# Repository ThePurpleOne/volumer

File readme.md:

# Volumer
Hardware module to easily control Individual Windows app just like the volume Mixer.

Accessing this window is a pain, especially if you're in game and you need to quickly lower that annoying SCREAMING discord friend in order to hear some terrorist footsteps.

> The PCB parts have been chosen for cheapest PCB Assembly with only 2 JLC PCB extended parts 

## How to setup
First you have to order your PCB and mount the potentiometers:
- [PCB Information](pcbs.md)
- [JLC PCB Order instructions](jlc_order.md)

Then you can install the software on the PC and flash the firmware on the Board:
- [Install the PC app](#pc-software)
- [Install/Update Board Firmware](#board-firmware)

## Case

There is no case for now, don't hesitate to contribute ! Here is the dimensions

## PC Software

[https://github.com/omriharel/deej](https://github.com/omriharel/deej)

For simplicity and not to reinvent the wheel, I'm using an opensource project called DEEJ, which actually does exactly what I want to do.

You only need to put the executable in the same folder as the config file and make a shortcut to the executable in the startup folder to have it start with windows.

config : [./src/pc/config.yaml](./src/pc/config.yaml) 

In the config, You can set which potentiometer controls which application and set the COM port of the board (The COM port is not automatically detected).

## Board Firmware 
You Circuit python or a UF2 compiled C program are available in the release page.

### C firmware
There is an already compiled UF2 file in the releases.

You can also compile the code yourself (need the RPI PICO SDK) and flash it to the board (Drag'n'drop in BOOTSEL mode). 

Compile with:
```bash
cd src/board/c
mkdir build
cd build
cmake ..
make
```

You can then flash the board with the generated UF2 file in the bin folder.

### Circuit Python
You can also use Circuitpython, which for a firmware that simple, i would not recommend it since it's just less reliable and efficient.

You'll first need to install Circuitpython firmware in the board and then push the program into it (Firmware and program available in release). 

To install the circuitpython firmware, you can simply drag and drop the UF2 file on the board after a boot with the BOOTSEL button pressed.

When Circuitpython is running, you can drag and drop the code.py file into the board Circuitpython mass storage (Not the one when bootsel is pressed).

## Download repo
Since there are submodules, you need to clone with the --recurse-submodules flag:

```bash
git clone --recurse-submodules
```

If you cloned without submodules
```bash
git submodule update --init
```

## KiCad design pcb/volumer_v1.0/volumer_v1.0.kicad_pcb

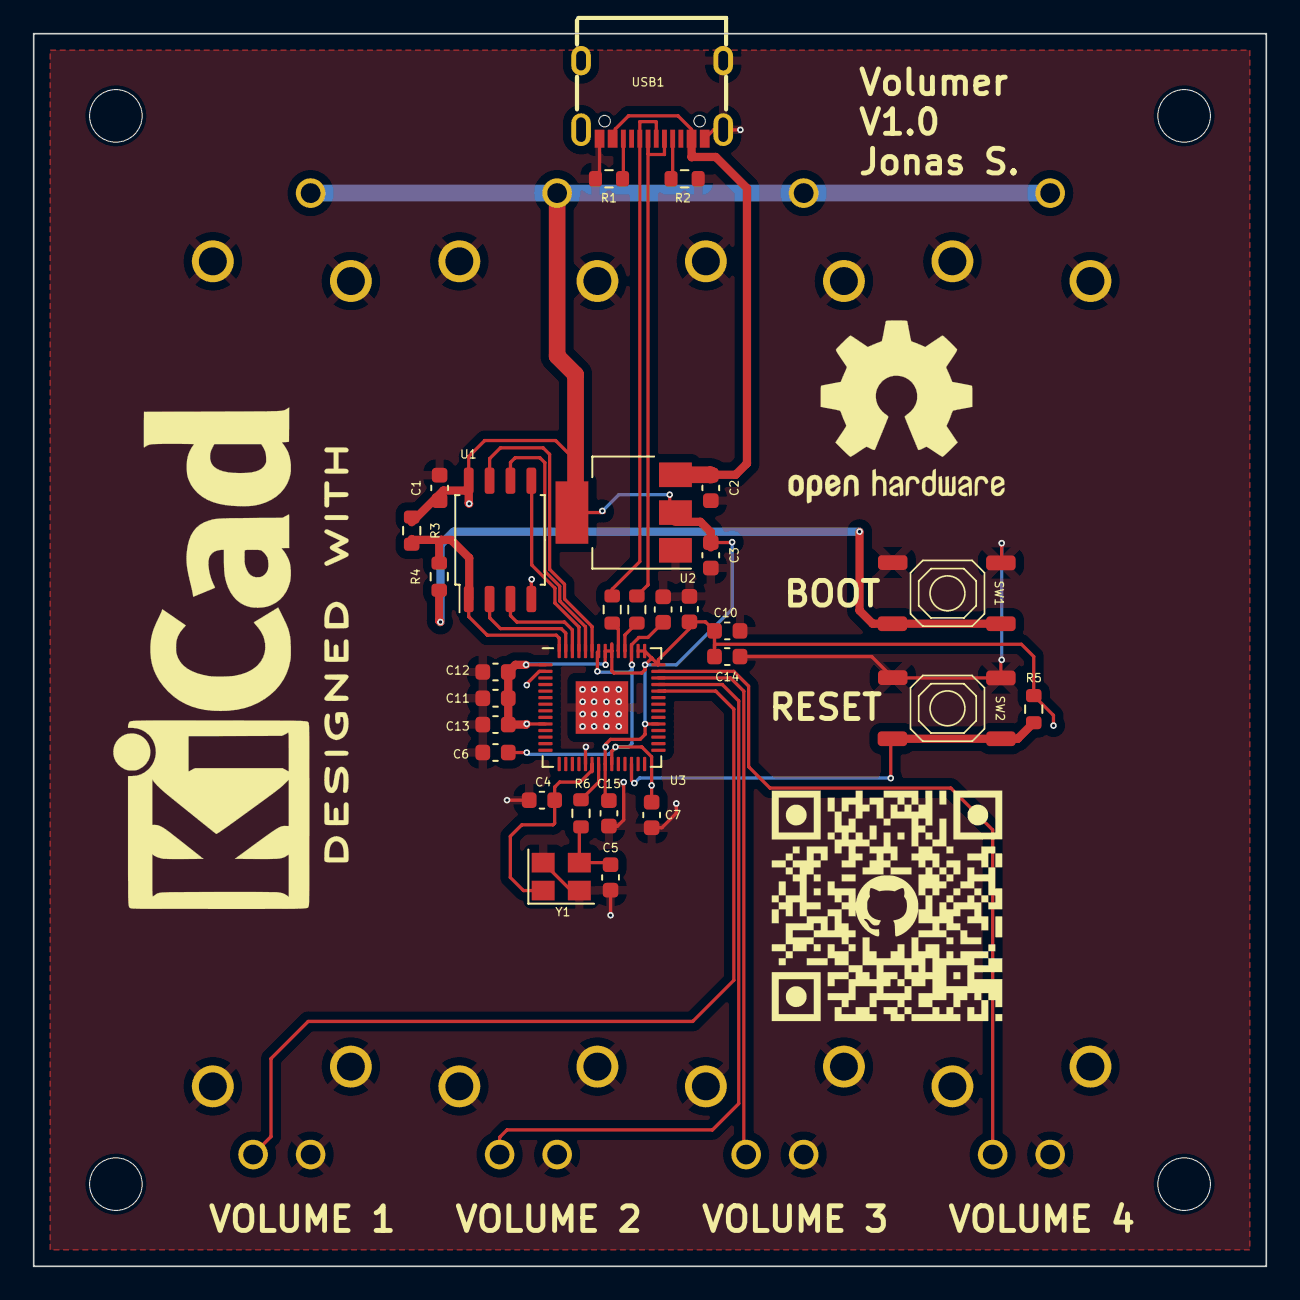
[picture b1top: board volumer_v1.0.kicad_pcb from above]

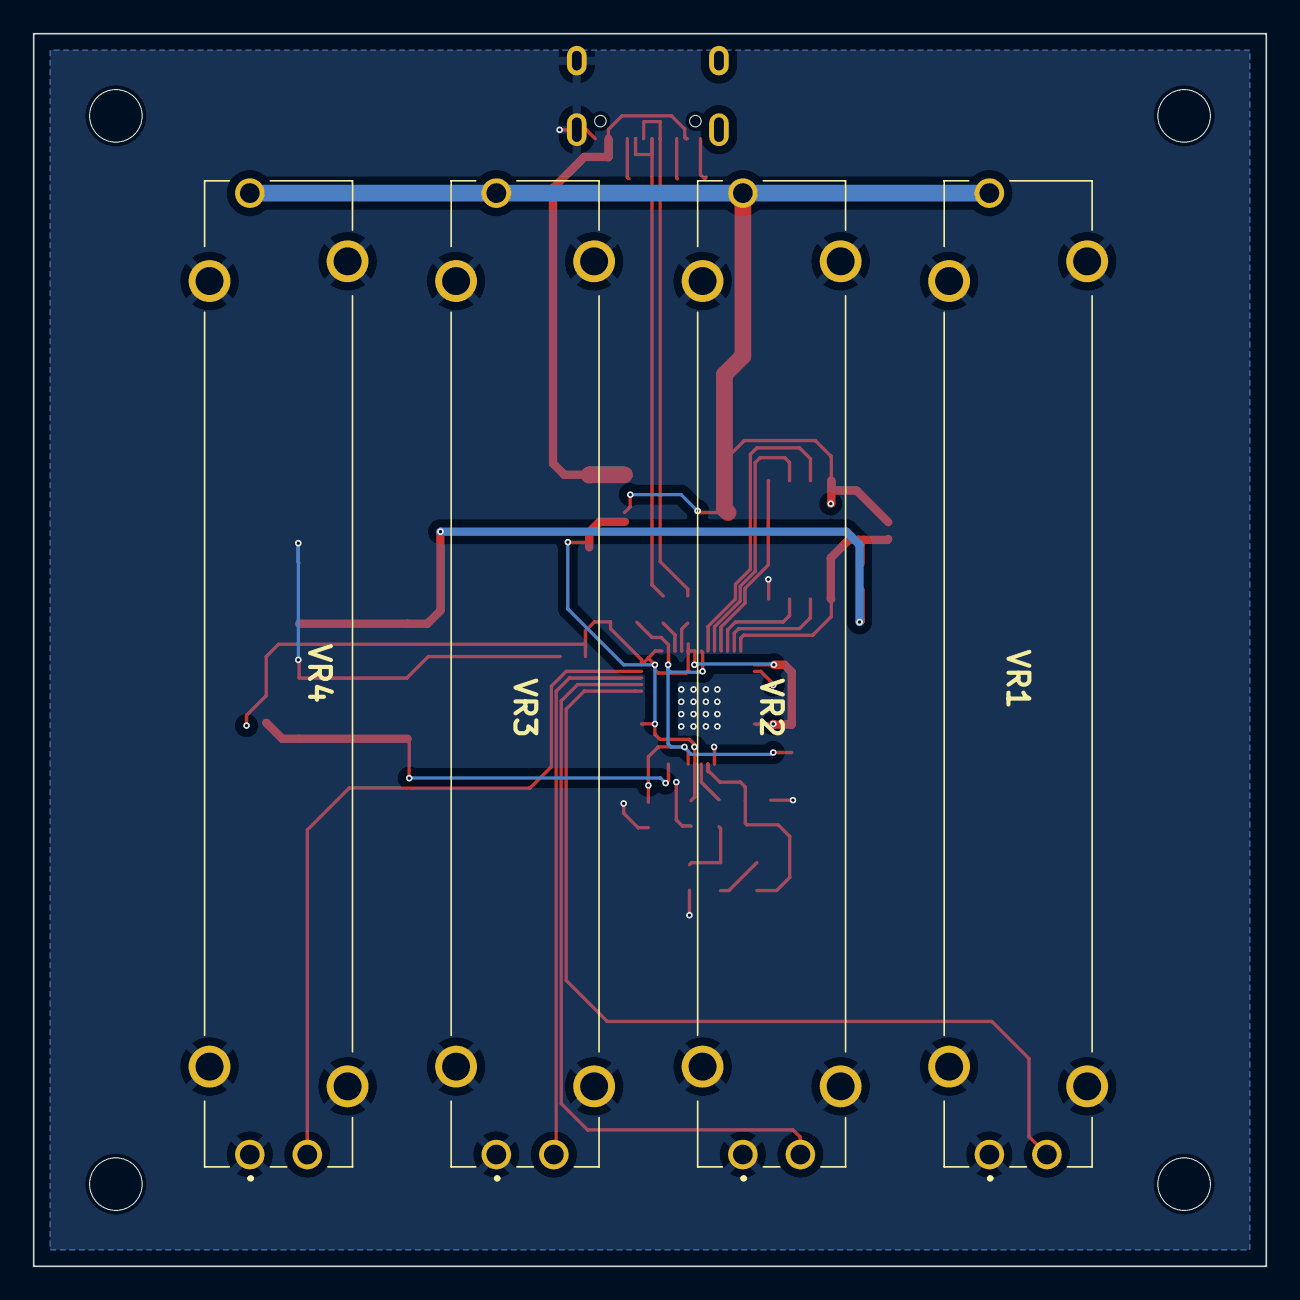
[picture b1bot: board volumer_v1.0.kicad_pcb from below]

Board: 2 copper layers, 75.0 x 75.0 mm, 39 parts (4 on the bottom side), 25 nets.

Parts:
C1, C2, C6, C7, C10, C11, C12, C13, C14, C15: 100n; C_0603_1608Metric
C3: 10u; C_0603_1608Metric
C4, C5: 30p; C_0603_1608Metric
C8, C9: 1u; C_0603_1608Metric
MH: MountingHole_3.2mm_M3
MH#2, MH#3, MH#4: MountingHole_3.2mm_M3
QR: LOGO; qr
R1, R2: 5k1; R_0603_1608Metric
R3, R5: 10k; R_0603_1608Metric
R4, R6: 1k; R_0603_1608Metric
R7, R8: 33; R_0603_1608Metric
SW1, SW2: SW_MEC_5E; TS-1187A-B-A-B
U1: W25Q128JVS; SOIC-8_5.23x5.23mm_P1.27mm
U2: LD1117S33TR; SOT-223-3_TabPin2
U3: RP2040; QFN-56-1EP_7x7mm_P0.4mm_EP3.2x3.2mm
USB1: USBC_16P
VR1, VR2, VR3, VR4: slide_pot; PTA45432015CPB503
Y1: 12Mhz; Crystal_SMD_3225-4Pin_3.2x2.5mm

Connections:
+3V3: C1.1, C3.1, C9.1, C10.1, C11.1, C12.1, C13.1, C14.1, C15.1, R3.1, R5.1, U1.8 (VCC), U2.2 (VO), U3.1 (IOVDD), U3.10 (IOVDD), U3.22 (IOVDD), U3.33 (IOVDD), U3.42 (IOVDD), U3.43 (ADC_AVDD), U3.44 (VREG_IN), U3.48 (USB_VDD), U3.49 (IOVDD), VR1.3 (VCC), VR2.3 (VCC), VR3.3 (VCC), VR4.3 (VCC)
+5V: C2.1, U2.3 (VI), USB1.2 (VBUS), USB1.11 (VBUS)
/USB_D+: R7.2, USB1.6 (D+), USB1.8 (D+)
/USB_D-: R8.2, USB1.5 (D-), USB1.7 (D-)
/rp2040/1V1: C6.1, C7.1, C8.1, U3.23 (DVDD), U3.45 (VREG_VOUT), U3.50 (DVDD)
/rp2040/N_USB_D+: R7.1, U3.47 (USB_DP)
/rp2040/N_USB_D-: R8.1, U3.46 (USB_DM)
/rp2040/QSPI_CLK: U1.6 (CLK), U3.52 (QSPI_SCLK)
/rp2040/QSPI_SD0: U1.5 (DI(IO0)), U3.53 (QSPI_SD0)
/rp2040/QSPI_SD1: U1.2 (DO(IO1)), U3.55 (QSPI_SD1)
/rp2040/QSPI_SD2: U1.3 (IO2), U3.54 (QSPI_SD2)
/rp2040/QSPI_SD3: U1.7 (IO3), U3.51 (QSPI_SD3)
/rp2040/QSPI_SS: R3.2, R4.2, U1.1 (~CS), U3.56 (QSPI_SS)
/rp2040/XIN: C4.1, U3.20 (XIN), Y1.1
/rp2040/XOUT: R6.1, U3.21 (XOUT)
/rp2040/~RST: R5.2, SW2.3 (K), SW2.4 (A), U3.26 (RUN)
/rp2040/~USB_BOOT: R4.1, SW1.3 (K), SW1.4 (A)
/vol_1: U3.38 (GPIO26_ADC0), VR1.2 (WP)
/vol_2: U3.39 (GPIO27_ADC1), VR2.2 (WP)
/vol_3: U3.40 (GPIO28_ADC2), VR3.2 (WP)
/vol_4: U3.41 (GPIO29_ADC3), VR4.2 (WP)
GND: C1.2, C2.2, C3.2, C4.2, C5.2, C6.2, C7.2, C8.2, C9.2, C10.2, C11.2, C12.2, C13.2, C14.2, C15.2, R1.2, R2.2, SW1.1, SW1.2, SW2.1, SW2.2, U1.4 (GND), U2.1 (GND), U3.19 (TESTEN), U3.57 (GND), USB1.1 (GND), USB1.12 (GND), USB1.13 (SHLD), VR1.1 (GND), VR1.MH1, VR1.MH2, VR1.MH3, VR1.MH4, VR2.1 (GND), VR2.MH1, VR2.MH2, VR2.MH3, VR2.MH4, VR3.1 (GND), VR3.MH1, VR3.MH2, VR3.MH3, VR3.MH4, VR4.1 (GND), VR4.MH1, VR4.MH2, VR4.MH3, VR4.MH4, Y1.2, Y1.4
unnamed: C5.1, R6.2, Y1.3
unnamed: R2.1, USB1.4 (CC1)
unnamed: R1.1, USB1.10 (CC2)

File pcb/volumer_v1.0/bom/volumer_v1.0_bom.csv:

"Reference","Value","Footprint","Qty","LCSC"
"C1,C2,C6,C7,C10,C11,C12,C13,C14,C15","100n","Capacitor_SMD:C_0603_1608Metric","10","C14663"
"C3","10u","Capacitor_SMD:C_0603_1608Metric","1","C19702"
"C4,C5","30p","Capacitor_SMD:C_0603_1608Metric","2","C1658"
"C8,C9","1u","Capacitor_SMD:C_0603_1608Metric","2","C15849"
"R1,R2","5k1","Resistor_SMD:R_0603_1608Metric","2","C23186"
"R3,R5","10k","Resistor_SMD:R_0603_1608Metric","2","C25804"
"R4,R6","1k","Resistor_SMD:R_0603_1608Metric","2","C21190"
"R7,R8","33","Resistor_SMD:R_0603_1608Metric","2","C23140"
"SW1,SW2","SW_MEC_5E","push_button:TS-1187A-B-A-B","2","C318884"
"U1","W25Q128JVS","Package_SO:SOIC-8_5.23x5.23mm_P1.27mm","1","C97521"
"U2","LD1117S33TR","Package_TO_SOT_SMD:SOT-223-3_TabPin2","1","C6186"
"U3","RP2040","Package_DFN_QFN:QFN-56-1EP_7x7mm_P0.4mm_EP3.2x3.2mm","1","C2040"
"USB1","~","USBC:USBC_16P","1","C2765186"
"VR1,VR2,VR3,VR4","slide_pot","PTA45432015CPB503","4",""
"Y1","12Mhz","Crystal:Crystal_SMD_3225-4Pin_3.2x2.5mm","1","C9002"

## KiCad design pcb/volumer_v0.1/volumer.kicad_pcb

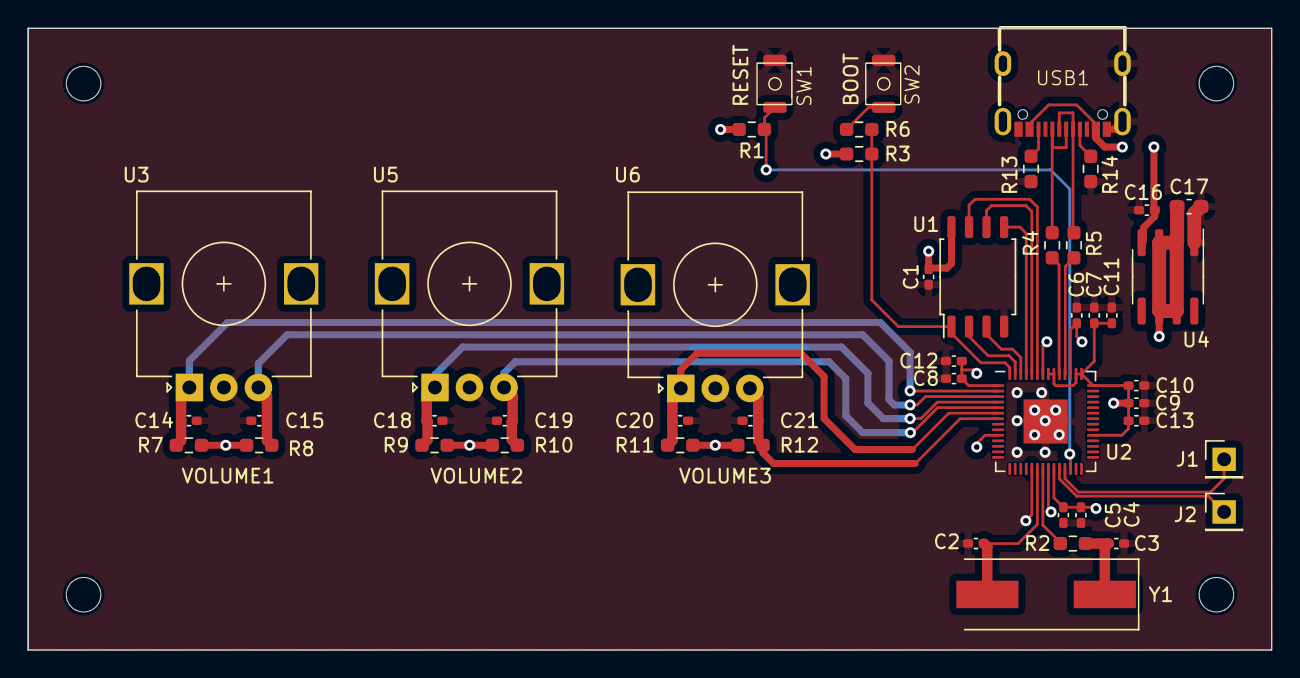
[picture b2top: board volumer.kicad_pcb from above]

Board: 4 copper layers, 90.0 x 45.0 mm, 47 parts (0 on the bottom side), 29 nets.

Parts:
C1, C4, C5, C8, C9, C10, C11, C12, C13, C16: 100n; C_0402_1005Metric_Pad0.74x0.62mm_HandSolder
C2, C3: 27p; C_0402_1005Metric_Pad0.74x0.62mm_HandSolder
C6, C7, C14, C15, C18, C19, C20, C21: 1u; C_0402_1005Metric_Pad0.74x0.62mm_HandSolder
C17: 10u; C_0603_1608Metric_Pad1.08x0.95mm_HandSolder
J1, J2: Conn_01x01_Pin; PinHeader_1x01_P2.54mm_Vertical
R1, R3, R7, R8, R9, R10, R11, R12: 10k; R_0603_1608Metric_Pad0.98x0.95mm_HandSolder
R2, R6: 1k; R_0603_1608Metric_Pad0.98x0.95mm_HandSolder
R4, R5: 27; R_0603_1608Metric_Pad0.98x0.95mm_HandSolder
R13, R14: 5k1; R_0603_1608Metric_Pad0.98x0.95mm_HandSolder
SW1, SW2: TS-3025-B-C-B; lcsc_TS-3025-A-A-B_push_button
U1: W25Q128JVS; SOIC-8_5.23x5.23mm_P1.27mm
U2: RP2040; QFN-56-1EP_7x7mm_P0.4mm_EP3.2x3.2mm
U3, U5, U6: Rotary encoder; RotaryEncoder_Alps_EC12E_Vertical_H20mm
U4: LD1117D33; SOIC-8_3.9x4.9mm_P1.27mm
USB1: USBC_16P
Y1: 12Mhz; Crystal_SMD_HC49-SD

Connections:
+3V3: C1.1, C7.1, C8.1, C9.1, C10.1, C11.1, C12.1, C13.1, C17.1, R1.1, R3.1, R7.1, R8.1, R9.1, R10.1, R11.1, R12.1, U1.8 (VCC), U2.1 (IOVDD), U2.10 (IOVDD), U2.22 (IOVDD), U2.33 (IOVDD), U2.42 (IOVDD), U2.43 (ADC_AVDD), U2.44 (VREG_IN), U2.48 (USB_VDD), U2.49 (IOVDD), U4.2 (VOUT), U4.3 (VOUT@2), U4.6 (VOUT@3), U4.7 (VOUT@4)
+5V: C16.1, U4.4 (VIN), USB1.2 (VBUS), USB1.11 (VBUS)
/RE1_A: C14.1, R7.2, U2.2 (GPIO0), U3.A (CCW)
/RE1_B: C15.1, R8.2, U2.3 (GPIO1), U3.B (WIPER)
/RE2_A: C18.1, R9.2, U2.4 (GPIO2), U5.A (CCW)
/RE2_B: C19.1, R10.2, U2.5 (GPIO3), U5.B (WIPER)
/RE3_A: C20.1, R11.2, U2.6 (GPIO4), U6.A (CCW)
/RE3_B: C21.1, R12.2, U2.7 (GPIO5), U6.B (WIPER)
/SWCLK: J2.1, U2.24 (SWCLK)
/SWD: J1.1, U2.25 (SWD)
/USB_D+: R4.2, USB1.6 (D+), USB1.8 (D+)
/USB_D-: R5.2, USB1.5 (D-), USB1.7 (D-)
/rp2040/1V1: C4.1, C5.1, C6.1, U2.23 (DVDD), U2.45 (VREG_VOUT), U2.50 (DVDD)
/rp2040/N_USB_D+: R4.1, U2.47 (USB_DP)
/rp2040/N_USB_D-: R5.1, U2.46 (USB_DM)
/rp2040/QSPI_CLK: U1.6 (CLK), U2.52 (QSPI_SCLK)
/rp2040/QSPI_SD0: U1.5 (DI(IO0)), U2.53 (QSPI_SD0)
/rp2040/QSPI_SD1: U1.2 (DO(IO1)), U2.55 (QSPI_SD1)
/rp2040/QSPI_SD2: U1.3 (IO2), U2.54 (QSPI_SD2)
/rp2040/QSPI_SD3: U1.7 (IO3), U2.51 (QSPI_SD3)
/rp2040/QSPI_SS: R3.2, R6.2, U1.1 (~CS), U2.56 (QSPI_SS)
/rp2040/XIN: C2.1, U2.20 (XIN), Y1.2
/rp2040/XOUT: R2.1, U2.21 (XOUT)
/rp2040/~RST: R1.2, SW1.2, U2.26 (RUN)
/rp2040/~USB_BOOT: R6.1, SW2.2
GND: C1.2, C2.2, C3.2, C4.2, C5.2, C6.2, C7.2, C8.2, C9.2, C10.2, C11.2, C12.2, C13.2, C14.2, C15.2, C16.2, C17.2, C18.2, C19.2, C20.2, C21.2, R13.2, R14.2, SW1.1, SW2.1, U1.4 (GND), U2.19 (TESTEN), U2.57 (GND), U3.C (CW), U4.1 (GND), U5.C (CW), U6.C (CW), USB1.1 (GND), USB1.12 (GND), USB1.13 (SHLD)
unnamed: C3.1, R2.2, Y1.1
unnamed: R14.1, USB1.4 (CC1)
unnamed: R13.1, USB1.10 (CC2)

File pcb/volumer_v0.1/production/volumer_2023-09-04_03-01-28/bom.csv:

Designator,Footprint,Quantity,Value,LCSC Part #
"C1, C10, C11, C12, C13, C16, C4, C5, C8, C9",0402,10,100n,
"C14, C15, C18, C19, C20, C21, C6, C7",0402,8,1u,
C17,0603,1,10u,
"C2, C3",0402,2,27p,
"J1, J2",PinHeader_1x01_P2.54mm_Vertical,2,Conn_01x01_Pin,
"R1, R10, R11, R12, R3, R7, R8, R9",0603,8,10k,
"R13, R14",0603,2,5k1,
"R2, R6",0603,2,1k,
"R4, R5",0603,2,27,
"SW1, SW2",lcsc_TS-3025-A-A-B_push_button,2,TS-3025-B-C-B ,C2689695
U1,SOIC-8_5.23x5.23mm_P1.27mm,1,W25Q128JVS,C97521
U2,QFN-56-1EP_7x7mm_P0.4mm_EP3.2x3.2mm,1,RP2040,C2040
"U3, U5, U6",RotaryEncoder_Alps_EC12E_Vertical_H20mm,3,Rotary encoder,C470603
U4,SOIC-8_3.9x4.9mm_P1.27mm,1,LD1117D33,C157440
USB1,USBC_16P,1,~,C2765186
Y1,Crystal_SMD_HC49-SD,1,12Mhz,C2889145

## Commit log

2023-09-15 Added PCB and basic doc
2023-09-15 Added untested programs
2023-09-23 Before going with serial
2023-09-23 Working serial comm for +-1 Rotary encoder
2023-09-23 Broken lib i guess
2023-09-25 Tried cs version and python, python freakin easier afaf
2023-09-25 Basic Python GUI
2023-10-01 Added some stuff to python version
2023-10-01 Removed hid lib
2023-10-01 Added serial ping pong on pc
2023-10-01 Got rid of pycache
2023-10-18 Finished PCB, not cheap enough, need to check components
2023-10-21 Added finished v0.2 PCB
2023-10-30 Working circuitpython code
2023-10-30 Added C program and instructions in readme
2023-10-30 Added images to the readme
2023-11-13 Added PCB V1.0
2023-11-13 Fixed broken link in readme
2023-11-13 Removed schematics from docs
2023-11-13 Create LICENSE
2024-03-26 Added pcb order instructions
2024-03-26 Added images
2024-03-28 Added dimensions image in readme
